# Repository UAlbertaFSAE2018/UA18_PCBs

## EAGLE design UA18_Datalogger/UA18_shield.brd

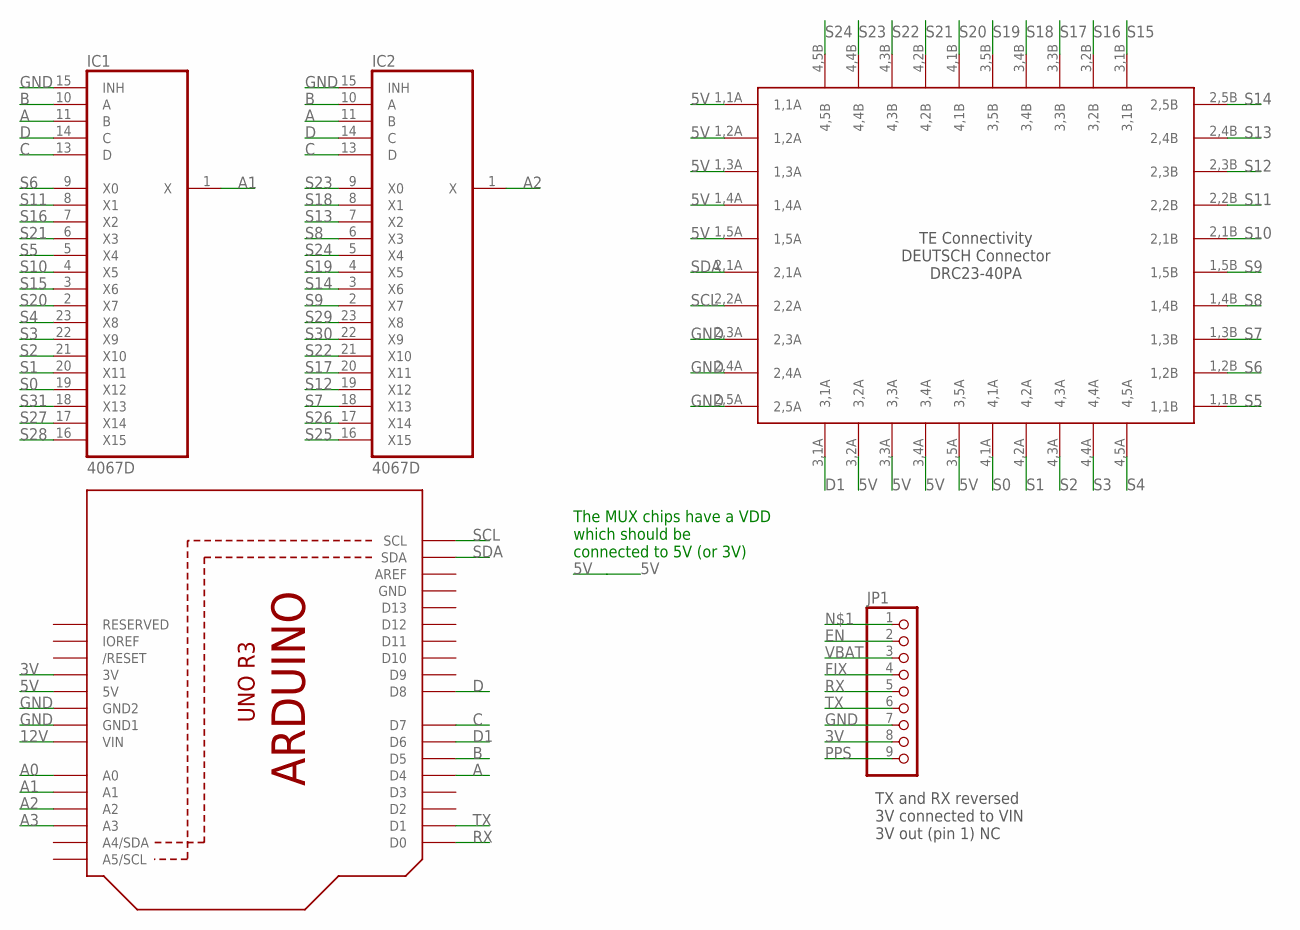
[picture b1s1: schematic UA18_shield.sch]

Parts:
IC1, IC2: 4067D; SO24W
JP1: PINHD-1X9; 1X09-BIG
U2: ARDUINOR3-DIMENSION; ARDUINOR3
U$1: DEUTSCH-DRC23-40PA-N012; DEUTSCH-40P-RECP-ASM

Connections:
3V: JP1.8, U2.3V
5V: IC1.24 (VDD), IC2.24 (VDD), U2.5V, U$1.1,1A, U$1.1,2A, U$1.1,3A, U$1.1,4A, U$1.1,5A, U$1.3,2A, U$1.3,3A, U$1.3,4A, U$1.3,5A
12V: U2.VIN
A: IC1.11 (B), IC2.11 (B), U2.D4
A0: U2.A0
A1: IC1.1 (X), U2.A1
A2: IC2.1 (X), U2.A2
A3: U2.A3
B: IC1.10 (A), IC2.10 (A), U2.D5
C: IC1.13 (D), IC2.13 (D), U2.D7
D: IC1.14 (C), IC2.14 (C), U2.D8
D1: U2.D6, U$1.3,1A
EN: JP1.2
FIX: JP1.4
GND: IC1.15 (INH), IC2.15 (INH), JP1.7, U2.GND, U2.GND1, U2.GND2, U$1.2,3A, U$1.2,4A, U$1.2,5A
PPS: JP1.9
RX: JP1.5, U2.D0
S0: IC1.19 (X12), U$1.4,1A
S1: IC1.20 (X11), U$1.4,2A
S2: IC1.21 (X10), U$1.4,3A
S3: IC1.22 (X9), U$1.4,4A
S4: IC1.23 (X8), U$1.4,5A
S5: IC1.5 (X4), U$1.1,1B
S6: IC1.9 (X0), U$1.1,2B
S7: IC2.18 (X13), U$1.1,3B
S8: IC2.6 (X3), U$1.1,4B
S9: IC2.2 (X7), U$1.1,5B
S10: IC1.4 (X5), U$1.2,1B
S11: IC1.8 (X1), U$1.2,2B
S12: IC2.19 (X12), U$1.2,3B
S13: IC2.7 (X2), U$1.2,4B
S14: IC2.3 (X6), U$1.2,5B
S15: IC1.3 (X6), U$1.3,1B
S16: IC1.7 (X2), U$1.3,2B
S17: IC2.20 (X11), U$1.3,3B
S18: IC2.8 (X1), U$1.3,4B
S19: IC2.4 (X5), U$1.3,5B
S20: IC1.2 (X7), U$1.4,1B
S21: IC1.6 (X3), U$1.4,2B
S22: IC2.21 (X10), U$1.4,3B
S23: IC2.9 (X0), U$1.4,4B
S24: IC2.5 (X4), U$1.4,5B
S25: IC2.16 (X15)
S26: IC2.17 (X14)
S27: IC1.17 (X14)
S28: IC1.16 (X15)
S29: IC2.23 (X8)
S30: IC2.22 (X9)
S31: IC1.18 (X13)
SCL: U2.SCL, U$1.2,2A
SDA: U2.SDA, U$1.2,1A
TX: JP1.6, U2.D1
VBAT: JP1.3
VSS: IC1.12 (VSS), IC2.12 (VSS)

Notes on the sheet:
TX and RX reversed 3V connected to VIN 3V out (pin 1) NC
The MUX chips have a VDD which should be connected to 5V (or 3V)

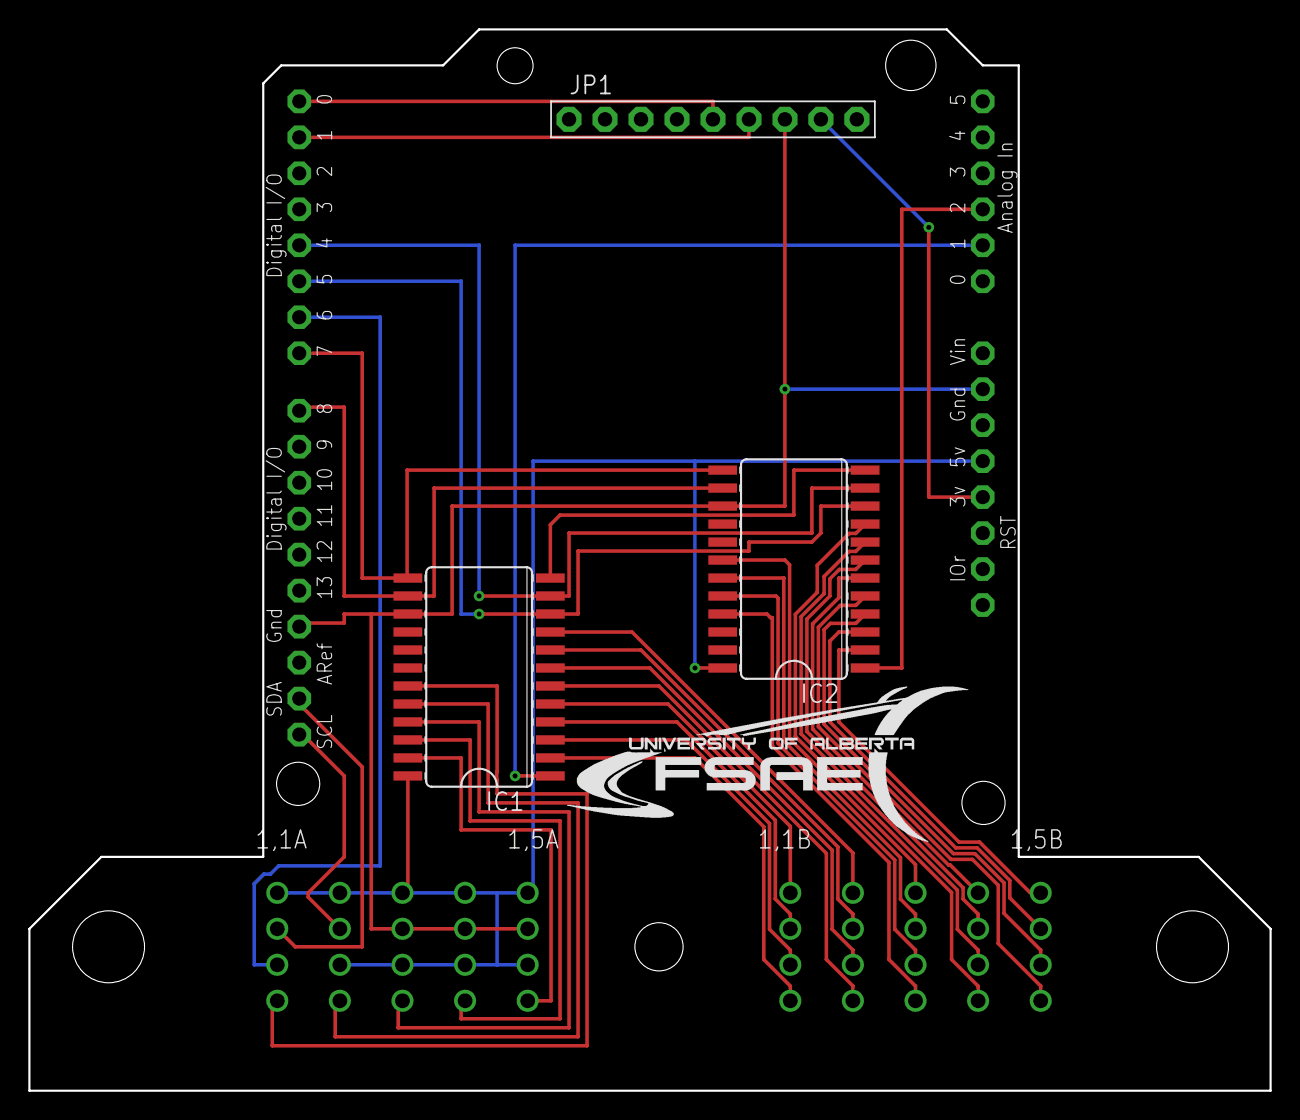
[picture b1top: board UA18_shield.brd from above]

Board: 2 copper layers, 87.6 x 74.9 mm, 5 parts (0 on the bottom side), 40 nets.

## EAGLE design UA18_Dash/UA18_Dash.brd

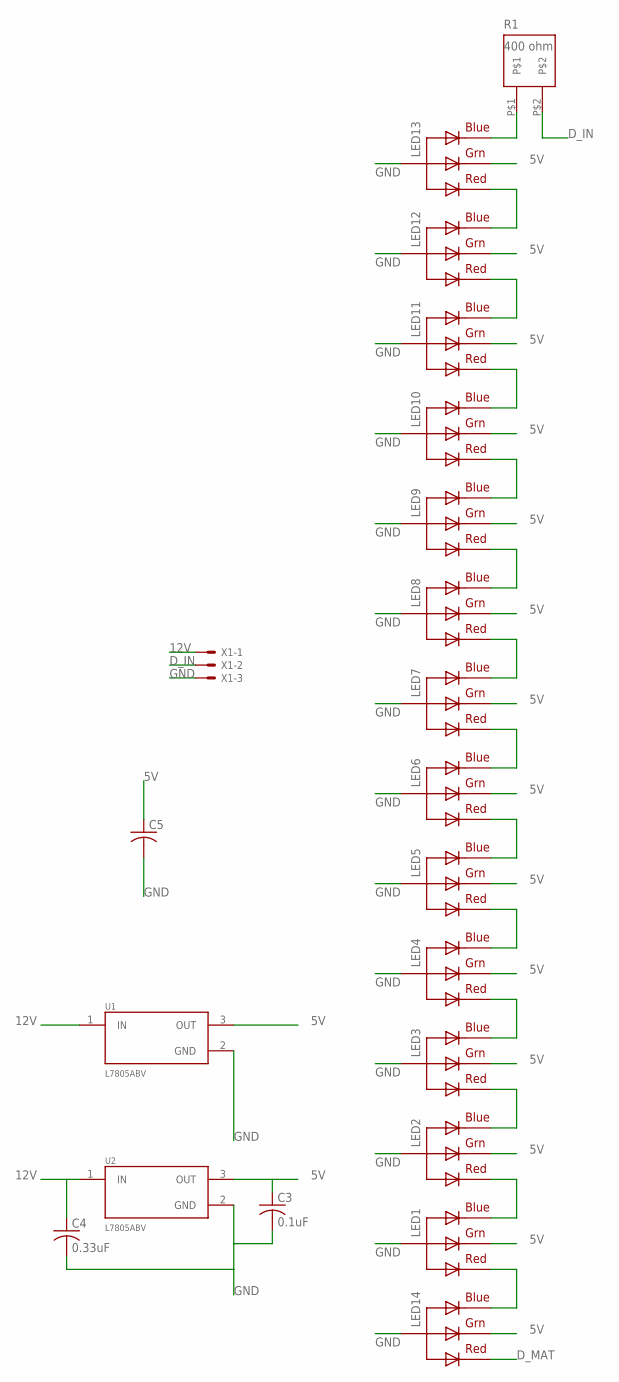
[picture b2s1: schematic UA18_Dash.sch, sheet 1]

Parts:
C3: 0.1uF; C050-024X044
C4: 0.33uF; C050-024X044
C5: C-US275-093X316; C275-093X316
LED1, LED2, LED3, LED4, LED5, LED6, LED7, LED8, LED9, LED10, LED11, LED12, LED13, LED14: RGBLED_CA-5MM; LED5MMRGB
R1: 400 ohm; TO-126
U1, U2: L7805ABV; TO254P460X1020X1945-3P
X1: KK-156-3

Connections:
5V: C3.1, C5.1, LED1.3 (GREEN), LED2.3 (GREEN), LED3.3 (GREEN), LED4.3 (GREEN), LED5.3 (GREEN), LED6.3 (GREEN), LED7.3 (GREEN), LED8.3 (GREEN), LED9.3 (GREEN), LED10.3 (GREEN), LED11.3 (GREEN), LED12.3 (GREEN), LED13.3 (GREEN), LED14.3 (GREEN), U1.3 (OUT), U2.3 (OUT); also elsewhere on the board
12V: C4.1, U1.1 (IN), U2.1 (IN), X1.1
DO_L1: LED6.4 (BLUE), LED7.1 (RED)
DO_L2: LED12.4 (BLUE), LED13.1 (RED)
DO_L3: LED11.4 (BLUE), LED12.1 (RED)
DO_L4: LED10.4 (BLUE), LED11.1 (RED)
DO_L5: LED9.4 (BLUE), LED10.1 (RED)
DO_L6: LED8.4 (BLUE), LED9.1 (RED)
DO_L7: LED7.4 (BLUE), LED8.1 (RED)
DO_L8: LED5.4 (BLUE), LED6.1 (RED)
DO_L10: LED3.4 (BLUE), LED4.1 (RED)
DO_L11: LED2.4 (BLUE), LED3.1 (RED)
DO_L12: LED1.1 (RED), LED1.4 (BLUE), LED2.1 (RED), LED14.4 (BLUE)
D_IN: R1.P$2, X1.2
D_MAT: LED14.1 (RED); also elsewhere on the board
GND: C3.2, C4.2, C5.2, LED1.2 (VCC), LED2.2 (VCC), LED3.2 (VCC), LED4.2 (VCC), LED5.2 (VCC), LED6.2 (VCC), LED7.2 (VCC), LED8.2 (VCC), LED9.2 (VCC), LED10.2 (VCC), LED11.2 (VCC), LED12.2 (VCC), LED13.2 (VCC), LED14.2 (VCC), U1.2 (GND), U2.2 (GND), X1.3; also elsewhere on the board
unnamed: LED13.4 (BLUE), R1.P$1
unnamed: LED4.4 (BLUE), LED5.1 (RED)

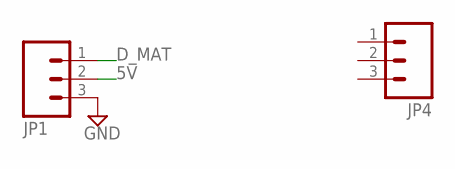
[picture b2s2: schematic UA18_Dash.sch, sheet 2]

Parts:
JP1, JP4: M03PTH; 1X03

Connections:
5V: JP1.2; also elsewhere on the board
D_MAT: JP1.1; also elsewhere on the board
GND: JP1.3; also elsewhere on the board

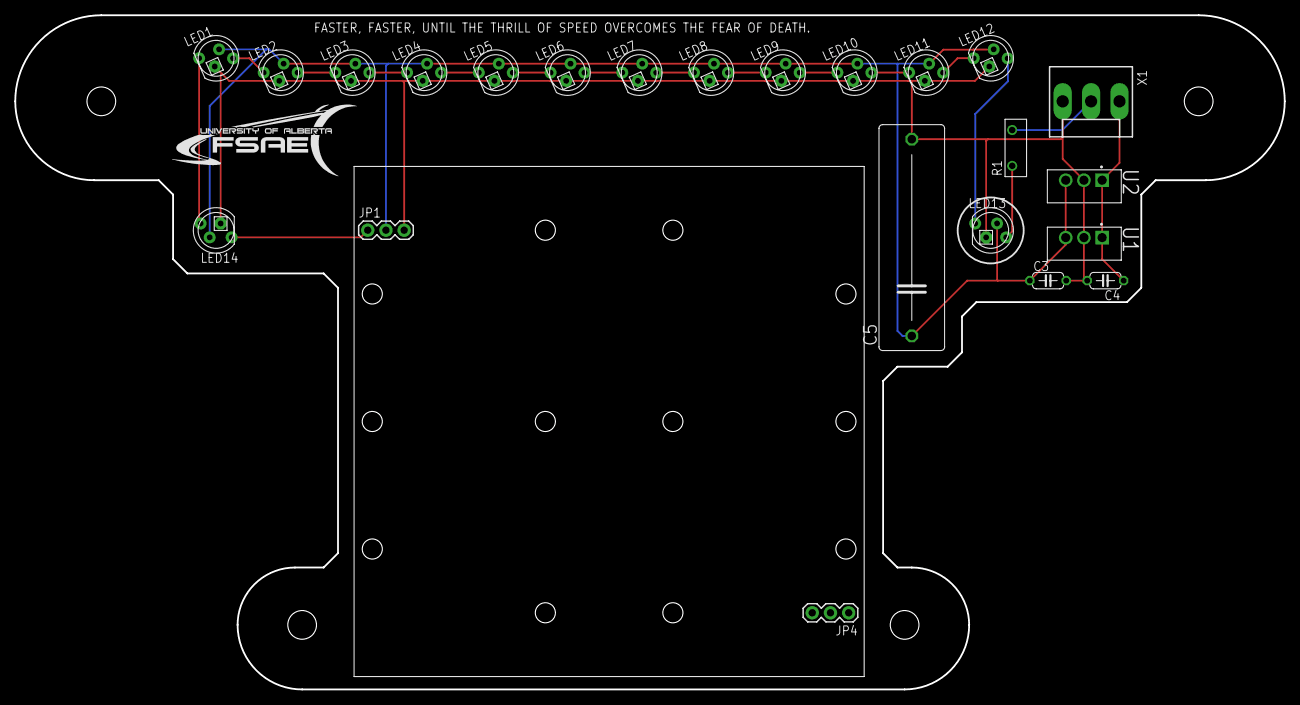
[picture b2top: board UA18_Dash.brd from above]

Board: 2 copper layers, 177.0 x 94.0 mm, 23 parts (0 on the bottom side), 18 nets.

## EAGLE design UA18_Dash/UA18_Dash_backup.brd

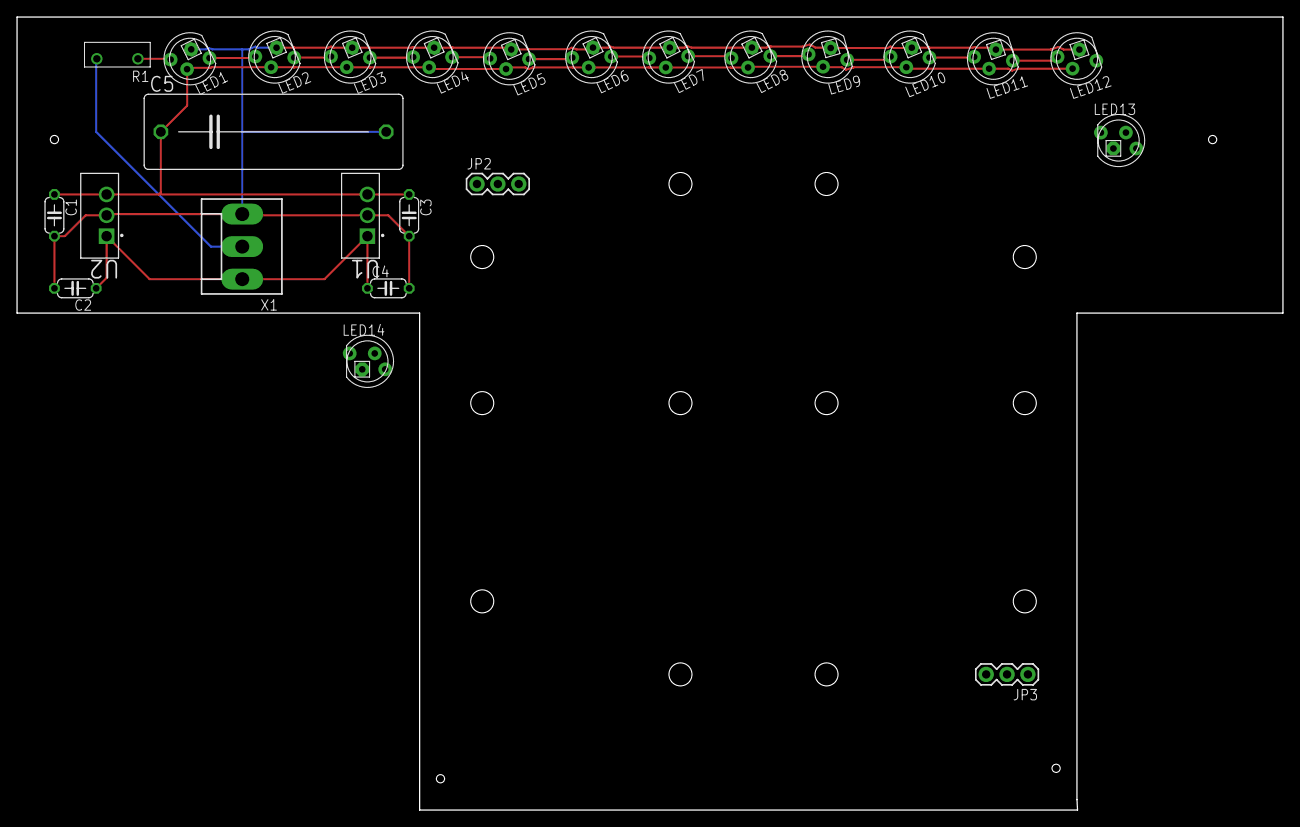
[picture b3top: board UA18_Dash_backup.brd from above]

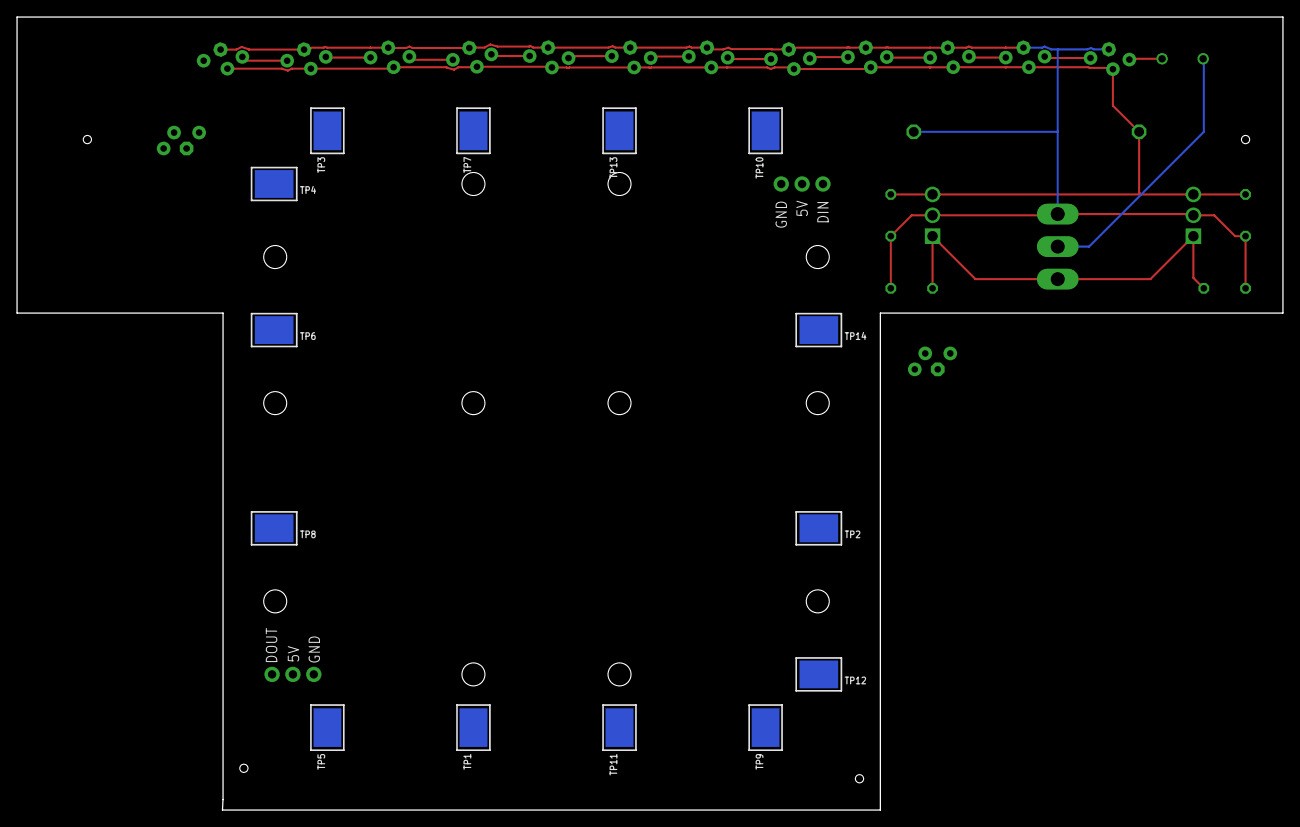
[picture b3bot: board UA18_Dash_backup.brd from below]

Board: 2 copper layers, 154.1 x 96.5 mm, 39 parts (14 on the bottom side), 18 nets.

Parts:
C1, C3: 0.1uF; C050-024X044
C2, C4: 0.33uF; C050-024X044
C5: C275-093X316
JP2, JP3: 1X03
LED1, LED2, LED3, LED4, LED5, LED6, LED7, LED8, LED9, LED10, LED11, LED12, LED13, LED14: RGBLED_CA-5MM; LED5MMRGB
R1: 400 ohm; TO-126
TP1, TP2, TP3, TP4, TP5, TP6, TP7, TP8, TP9, TP10, TP11, TP12, TP13, TP14: TESTPOINT_SMT
U1, U2: L7805ABV; TO254P460X1020X1945-3P
X1: KK-156-3

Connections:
5V: C1.1, C3.1, C5.1, JP2.2, LED1.3, LED2.3, LED3.3, LED4.3, LED5.3, LED6.3, LED7.3, LED8.3, LED9.3, LED10.3, LED11.3, LED12.3, LED13.3, LED14.3, U1.3, U2.3
12V: C2.1, C4.1, U1.1, U2.1, X1.1
DI_L12: LED1.4, R1.P$1
DO_L1: LED7.1, LED8.4
DO_L2: LED13.1, LED14.4
DO_L3: LED12.1, LED13.4
DO_L4: LED11.1, LED12.4
DO_L5: LED10.1, LED11.4
DO_L6: LED9.1, LED10.4
DO_L7: LED8.1, LED9.4
DO_L8: LED6.1, LED7.4
DO_L9: LED5.1, LED6.4
DO_L10: LED4.1, LED5.4
DO_L11: LED3.1, LED4.4
DO_L12: LED1.1, LED2.1, LED2.4, LED3.4
D_IN: R1.P$2, X1.2
D_MAT: JP2.1, LED14.1
GND: C1.2, C2.2, C3.2, C4.2, C5.2, JP2.3, JP3.3, LED1.2, LED2.2, LED3.2, LED4.2, LED5.2, LED6.2, LED7.2, LED8.2, LED9.2, LED10.2, LED11.2, LED12.2, LED13.2, LED14.2, TP1.P$1, TP2.P$1, TP3.P$1, TP4.P$1, TP5.P$1, TP6.P$1, TP7.P$1, TP8.P$1, TP9.P$1, TP10.P$1, TP11.P$1, TP12.P$1, TP13.P$1, TP14.P$1, U1.2, U2.2, X1.3

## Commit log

2018-05-07 added Eagle files
    For dash and datalogger
2018-05-07 finished datalogger
2018-05-08 updated datalogger and exported CAM job

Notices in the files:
parts and their libraries:
microbuilder: This work is placed in the public domain, and may be freely used for commercial and non-commercial work with the following conditions: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
